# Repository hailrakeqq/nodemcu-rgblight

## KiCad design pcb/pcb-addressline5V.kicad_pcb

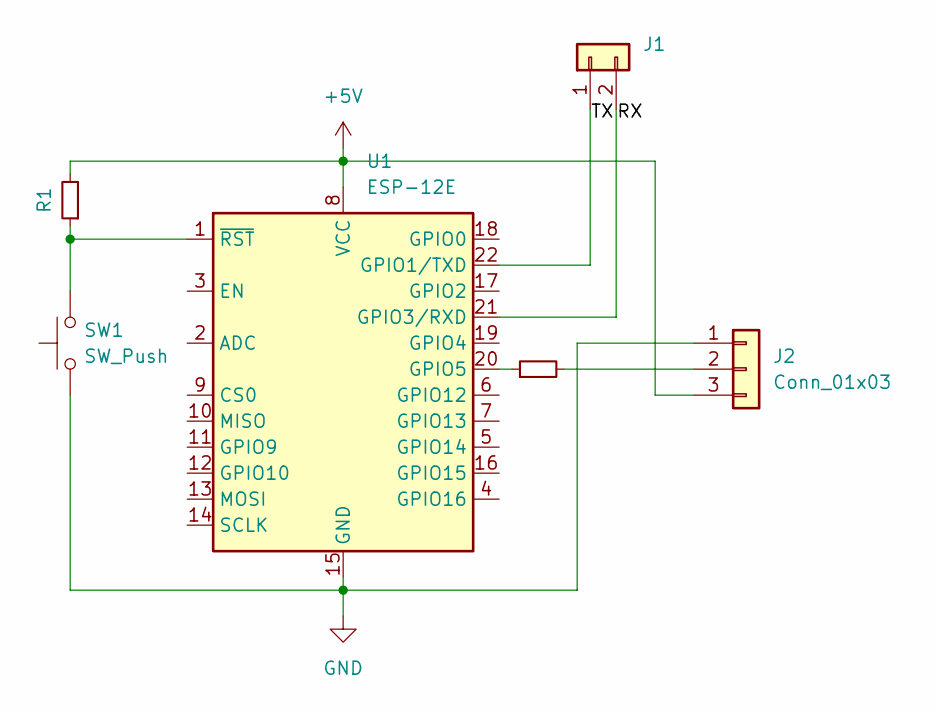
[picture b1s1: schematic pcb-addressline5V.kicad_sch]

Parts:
J1: Conn_01x02; PinHeader_1x02_P2.54mm_Vertical
J2: Conn_01x03; PinHeader_1x03_P2.54mm_Vertical
R1, R5: R_Small; R_Axial_DIN0204_L3.6mm_D1.6mm_P5.08mm_Horizontal
SW1: SW_Push; SW_PUSH_6mm
U1: ESP-12E

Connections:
+5V: J2.3, R1.2, U1.8 (VCC)
/RX: J1.2, U1.21 (GPIO3/RXD)
/TX: J1.1, U1.22 (GPIO1/TXD)
GND: J2.1, SW1.1, U1.15 (GND)
unnamed: J2.2, R5.2
unnamed: R5.1, U1.20 (GPIO5)
unnamed: R1.1, SW1.2, U1.1 (~RST)

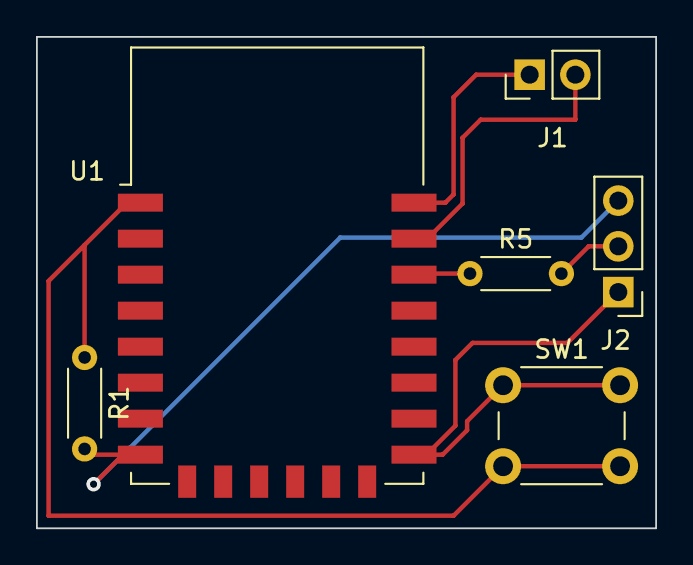
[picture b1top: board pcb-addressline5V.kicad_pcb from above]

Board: 2 copper layers, 34.4 x 27.3 mm, 6 parts (0 on the bottom side), 7 nets.

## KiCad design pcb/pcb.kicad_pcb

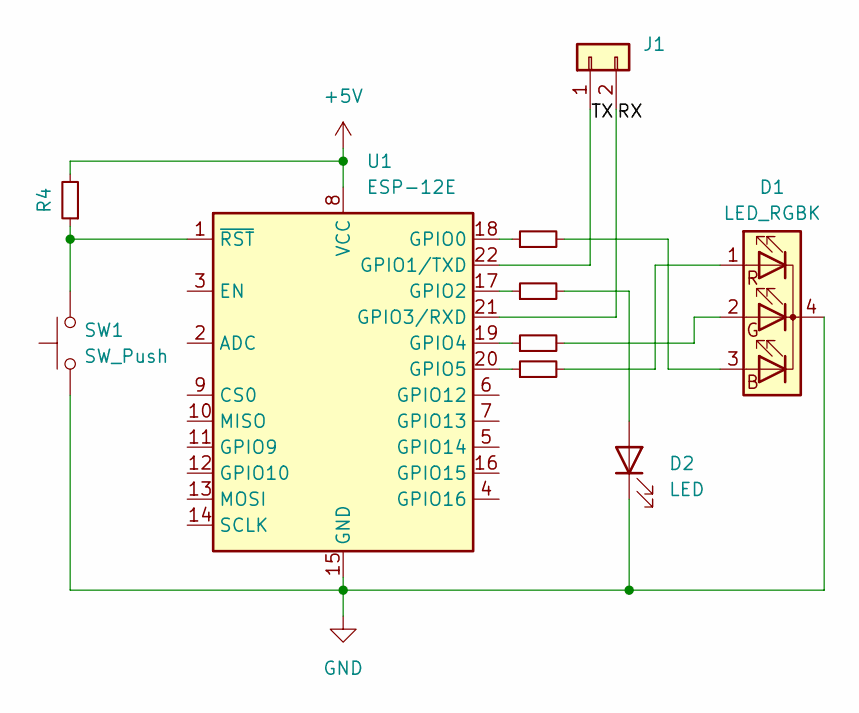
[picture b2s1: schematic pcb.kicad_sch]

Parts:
D1: LED_RGBK; PinHeader_1x04_P2.54mm_Vertical
D2: LED; LED_D3.0mm
J1: Conn_01x02; PinHeader_1x02_P2.54mm_Vertical
R1, R2, R3, R4, R5: R_Small; R_Axial_DIN0204_L3.6mm_D1.6mm_P5.08mm_Horizontal
SW1: SW_Push; SW_PUSH_6mm
U1: ESP-12E

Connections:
+5V: R4.2, U1.8 (VCC)
/RX: J1.2, U1.21 (GPIO3/RXD)
/TX: J1.1, U1.22 (GPIO1/TXD)
GND: D1.4 (K), D2.1 (K), SW1.1, U1.15 (GND)
unnamed: D1.3 (BA), R1.2
unnamed: D1.2 (GA), R2.2
unnamed: D1.1 (RA), R3.2
unnamed: D2.2 (A), R5.2
unnamed: R1.1, U1.18 (GPIO0)
unnamed: R5.1, U1.17 (GPIO2)
unnamed: R2.1, U1.19 (GPIO4)
unnamed: R3.1, U1.20 (GPIO5)
unnamed: R4.1, SW1.2, U1.1 (~RST)

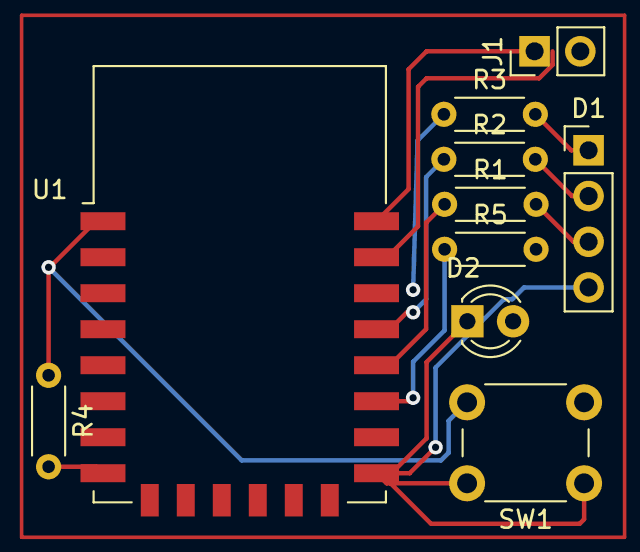
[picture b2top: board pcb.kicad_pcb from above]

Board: 2 copper layers, 10 parts (0 on the bottom side), 13 nets.

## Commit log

2024-01-03 add pcb
2024-01-03 Create LICENSE
2024-01-04 update desktop ui
2024-01-04 update networking
2024-01-04 update core sketch
